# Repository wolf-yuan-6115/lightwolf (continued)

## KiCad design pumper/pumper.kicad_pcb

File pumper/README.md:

# Pumper

Pumper is an experimental RP2354-based USB Audio Class 2 DAC. The board uses a
PCM5102A DAC with OPA1652 and OPA1622 analog stages in a compact design intended
for learning about USB audio and DAC hardware.

The firmware provides a ten-band parametric EQ, headphone crossfeed, output
processing, USB host volume and mute, and persistent EQ profiles. Settings can
be controlled from either the React WebHID controller or the native Android
controller. Both controllers preview edits live and save persistent settings
only through explicit save actions.

## Supported audio formats

Pumper accepts stereo PCM over USB Audio Class 2 in the following formats:

| Sample rate | 16-bit stereo | Packed 24-bit stereo |
| ----------- | ------------- | -------------------- |
| 44.1 kHz    | Yes           | Yes                  |
| 48 kHz      | Yes           | Yes                  |
| 88.2 kHz    | Yes           | Yes                  |
| 96 kHz      | Yes           | Yes                  |
| 176.4 kHz   | Yes           | No                   |
| 192 kHz     | Yes           | No                   |

## Audio processing and hardware path

Audio packets cross from the USB-facing core into the real-time DSP core
through a fixed block pool. After processing, ping-pong DMA feeds the PIO I2S
transmitter; the analog stages then filter, buffer, attenuate, and drive the
headphone output.

```mermaid
flowchart TB
    HOST[USB host<br/>UAC2 stereo PCM]

    subgraph DIGITAL[Digital audio path]
        direction LR
        USB[TinyUSB on RP2354 core 0<br/>receive and decode USB packets]
        QUEUE[Fixed audio-block queue<br/>core 0 to core 1]
        EQ[Preamp and<br/>10-band parametric EQ]
        XF[Headphone crossfeed]
        HOSTCTL[USB host<br/>gain and mute]
        OUTPROC[Output processing<br/>balance, mono, and width]
        LIMIT[Always-on<br/>stereo limiter]
        PACK[Final PCM quantization<br/>and I2S packing]
        I2S[Ping-pong DMA and PIO<br/>I2S transmitter]
        DAC[PCM5102A<br/>I2S DAC]

        USB --> QUEUE --> EQ --> XF --> HOSTCTL --> OUTPROC --> LIMIT --> PACK --> I2S --> DAC
    end

    subgraph ANALOG[Analog audio path]
        direction LR
        FILTER[Passive output filters]
        BUFFER[OPA1652<br/>stereo buffer]
        VOLUME[Dual-gang analog<br/>volume control]
        DRIVER[OPA1622<br/>headphone driver]
        PROTECT[Output ESD protection]
        JACK[3.5 mm TRRS<br/>analog output]

        FILTER --> BUFFER --> VOLUME --> DRIVER --> PROTECT --> JACK
    end

    HOST --> USB
    DAC --> FILTER
```

## Repository layout

- [`firmware/`](firmware/) — RP2354 firmware and portable host tests.
- [`web/`](web/) — React/TypeScript WebHID controller.
- [`android/`](android/) — experimental Android USB-host controller.
- [`assets/`](assets/) — board and assembled-device images.
- KiCad source files in the repository root — schematic and PCB design.

## Build and run

### Firmware

The firmware requires the Pico SDK, CMake, Ninja, a native C compiler, and the
Arm GNU embedded toolchain. See [`firmware/README.md`](firmware/README.md) for
SDK setup, supported audio formats, flashing, and troubleshooting.

```sh
export PICO_SDK_PATH="${HOME}/Projects/pico-sdk"
cmake -S firmware -B firmware/build -G Ninja \
  -DCMAKE_BUILD_TYPE=Release \
  -DPICO_BOARD=pico2 \
  -DPICO_PLATFORM=rp2350-arm-s \
  -DPICO_FLASH_SIZE_BYTES=2097152
cmake --build firmware/build --target rp2350_usb_dac -j
```

Flash `firmware/build/rp2350_usb_dac.uf2` using the RP2354 BOOTSEL drive.

### Web controller

Use a Chromium-based browser. WebHID works on a secure origin and on
`http://localhost`.

```sh
cd web
pnpm install
pnpm dev
```

See [`web/README.md`](web/README.md) for Linux HID permissions, tests,
production builds, previewing, and deployment.

### Android controller

The Android controller requires JDK 17 and Android SDK API 37. Android Studio
can open [`android/`](android/) directly.

```sh
cd android
./gradlew testDebugUnitTest lintDebug assembleDebug
```

See [`android/README.md`](android/README.md) for the debug simulator and USB
device requirements.

### Firmware host tests

These tests do not require the Pico SDK:

```sh
cmake -S firmware/tests -B /tmp/pumper-firmware-tests
cmake --build /tmp/pumper-firmware-tests
ctest --test-dir /tmp/pumper-firmware-tests --output-on-failure
```

## Hardware

## Bill of materials

| Item         | Cost        |
| ------------ | ----------- |
| PCB shipping | $6.12       |
| PCB assembly | $86.18      |
| PCB          | $11.43      |
| **Total**    | **$103.73** |

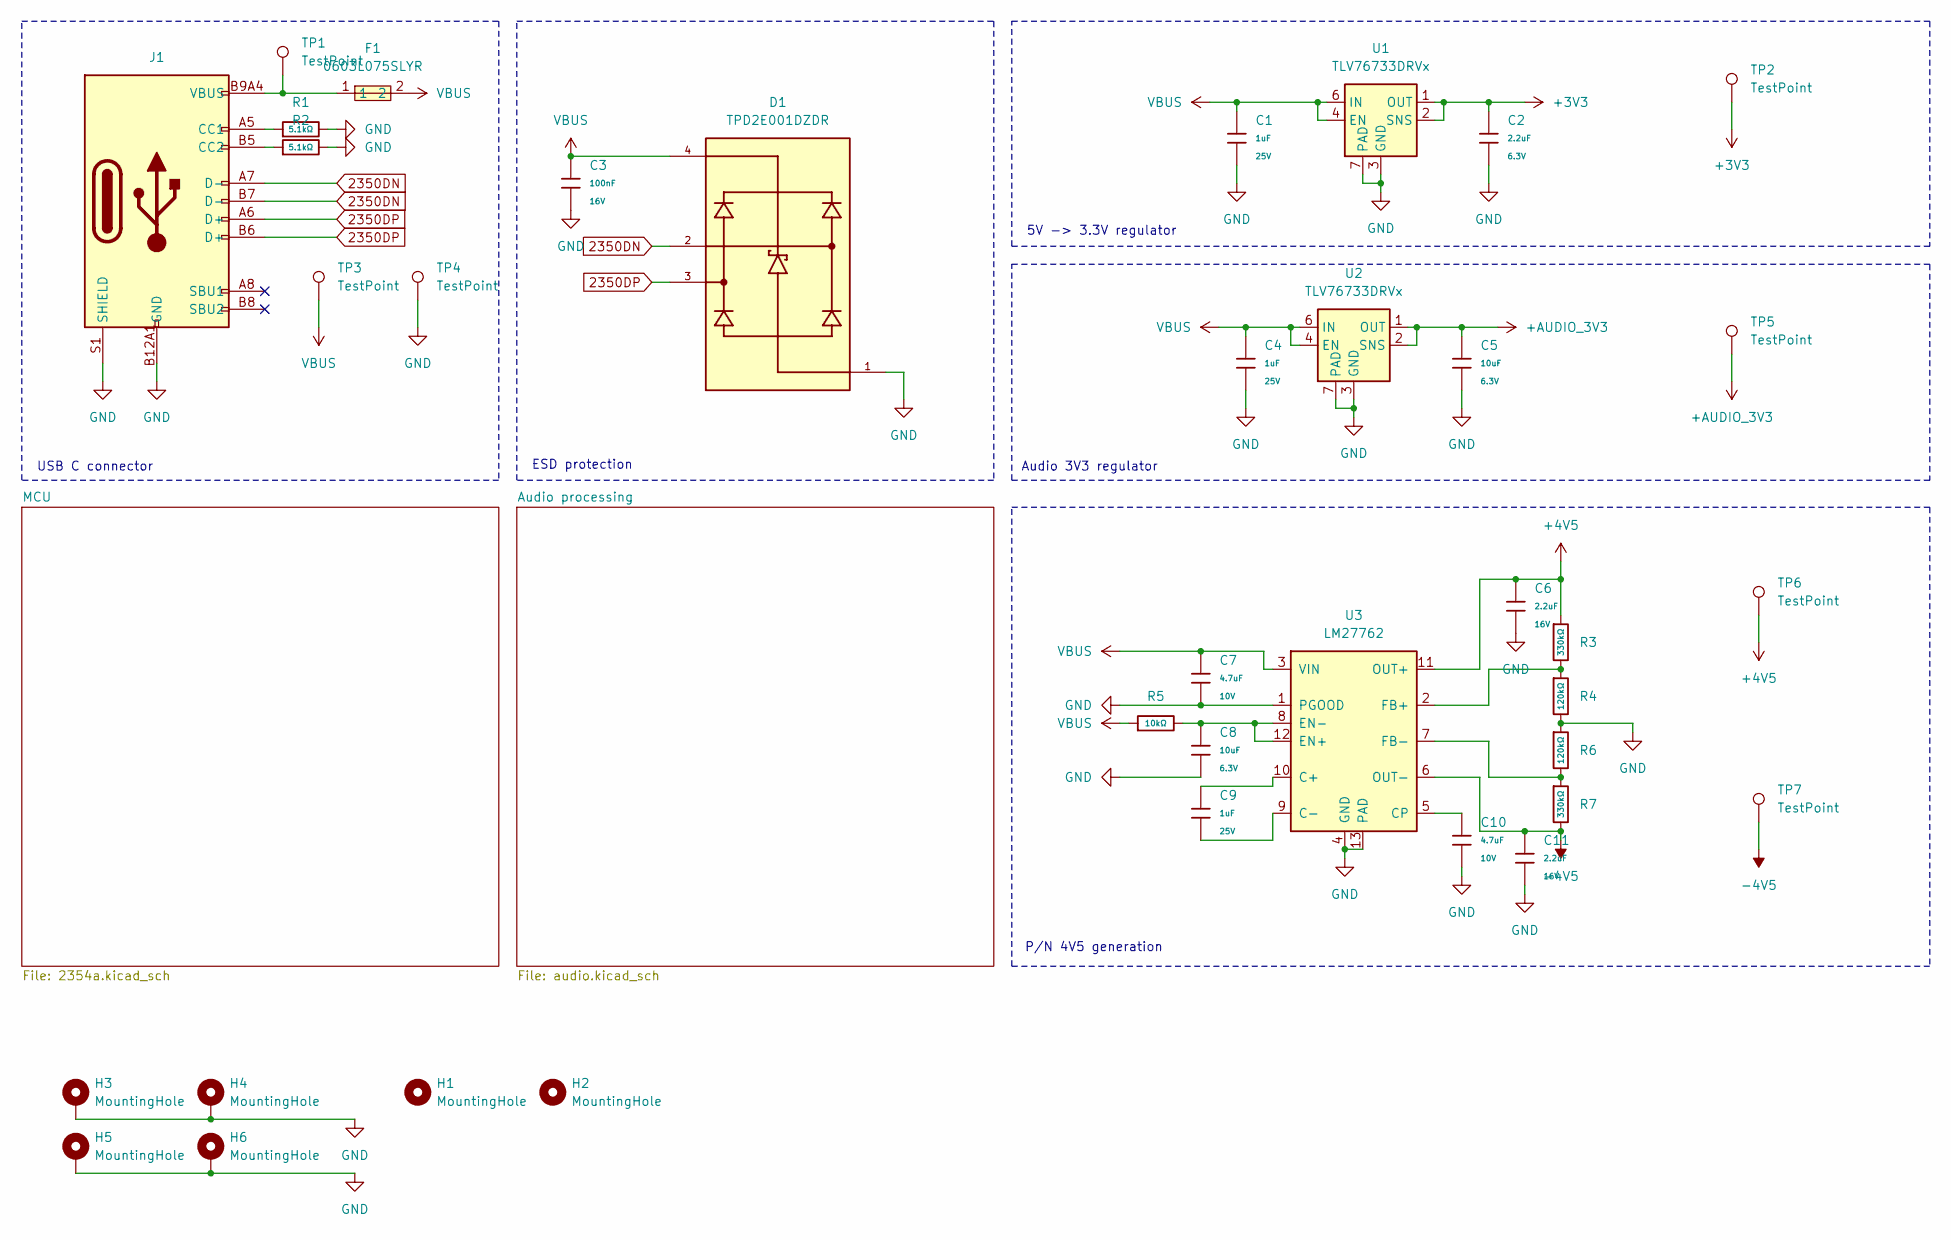
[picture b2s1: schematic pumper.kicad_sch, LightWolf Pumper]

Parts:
C1, C4, C9: 1uF; C_0402; Voltage Rated 25V; Tolerance ±10%; Part CL05A105KA5NQNC; LCSC C52923
C2: 2.2uF; C_0402; Voltage Rated 6.3V; Tolerance ±20%; Part CL05A225MQ5NSNC; LCSC C12530
C3: 100nF; C_0402; Voltage Rated 16V; Tolerance ±10%; Part CL05B104KO5NNNC; LCSC C1525
C5, C8: 10uF; C_0402; Voltage Rated 6.3V; Tolerance ±20%; Part CL05A106MQ5NUNC; LCSC C15525
C6, C11: 2.2uF; C_0603; Voltage Rated 16V; Tolerance ±10%; Part CL10A225KO8NNNC; LCSC C23630
C7, C10: 4.7uF; C_0402; Voltage Rated 10V; Tolerance ±20%; Part CL05A475MP5NRNC; LCSC C23733
D1: TPD2E001DZDR; SOT192P237X122-4N; PARTREV I
F1: 0603L075SLYR; F0603; LCSC Part C207016
H1, H2: MountingHole; ToolingHole_1.152mm
H3, H4, H5, H6: MountingHole; MountingHole_2.2mm_M2_Pad_Via
J1: Connector, USB-TYPE-C-16P; TYPE-C-SMD_HX-TYPE-C-16PIN; LCSC C2927039
R1, R2: 5.1kΩ; R_0402; Overload Voltage (Max) 50V; Tolerance ±1%; Part 0402WGF5101TCE; LCSC C25905
R3, R7: 330kΩ; R_0402; Overload Voltage (Max) 50V; Tolerance ±1%; Part 0402WGF3303TCE; LCSC C25778
R4, R6: 120kΩ; R_0402; Overload Voltage (Max) 50V; Tolerance ±1%; Part 0402WGF1203TCE; LCSC C25750
R5: 10kΩ; R_0402; Overload Voltage (Max) 50V; Tolerance ±1%; Part 0402WGF1002TCE; LCSC C25744
TP1, TP2, TP3, TP4, TP5, TP6, TP7: TestPoint; TestPoint_Pad_D1.0mm
U1, U2: TLV76733DRVx; WSON-6-1EP_2x2mm_P0.65mm_EP1x1.6mm_ThermalVias
U3: LM27762; WSON-12-1EP_3x2mm_P0.5mm_EP1x2.65_ThermalVias

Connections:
2350DN: D1.2, J1.A7 (D-), J1.B7 (D-); also elsewhere on the board
2350DP: D1.3, J1.A6 (D+), J1.B6 (D+); also elsewhere on the board
+3V3: C2.1, TP2.1, U1.1 (OUT), U1.2 (SNS); also elsewhere on the board
+4V5: C6.1, R3.1, TP6.1, U3.11 (OUT+); also elsewhere on the board
+AUDIO_3V3: C5.1, TP5.1, U2.1 (OUT), U2.2 (SNS); also elsewhere on the board
-4V5: C11.1, R7.2, TP7.1, U3.6 (OUT-); also elsewhere on the board
GND: C1.2, C2.2, C3.2, C4.2, C5.2, C6.2, C7.2, C8.2, C10.2, C11.2, D1.1, H3.1, H4.1, H5.1, H6.1, J1.A12B1 (GND), J1.B12A1 (GND), J1.S1 (SHIELD), R1.2, R2.2, R4.2, R6.1, TP4.1, U1.3 (GND), U1.5 (GND), U1.7 (PAD), U2.3 (GND), U2.5 (GND), U2.7 (PAD), U3.1 (PGOOD), U3.4 (GND), U3.13 (PAD); also elsewhere on the board
unnamed: F1.1, J1.A9B4 (VBUS), J1.B9A4 (VBUS), TP1.1
unnamed: J1.A5 (CC1), R1.1
unnamed: J1.B5 (CC2), R2.1
unnamed: C9.1, U3.10 (C+)
unnamed: C9.2, U3.9 (C-)
unnamed: C10.1, U3.5 (CP)
unnamed: C8.1, R5.2, U3.8 (EN-), U3.12 (EN+)
unnamed: R3.2, R4.1, U3.2 (FB+)
unnamed: R6.2, R7.1, U3.7 (FB-)
VBUS: C1.1, C3.1, C4.1, C7.1, D1.4, F1.2, R5.1, TP3.1, U1.4 (EN), U1.6 (IN), U2.4 (EN), U2.6 (IN), U3.3 (VIN)

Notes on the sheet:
ESD protection
Audio 3V3 regulator
P/N 4V5 generation
USB C connector
5V -> 3.3V regulator

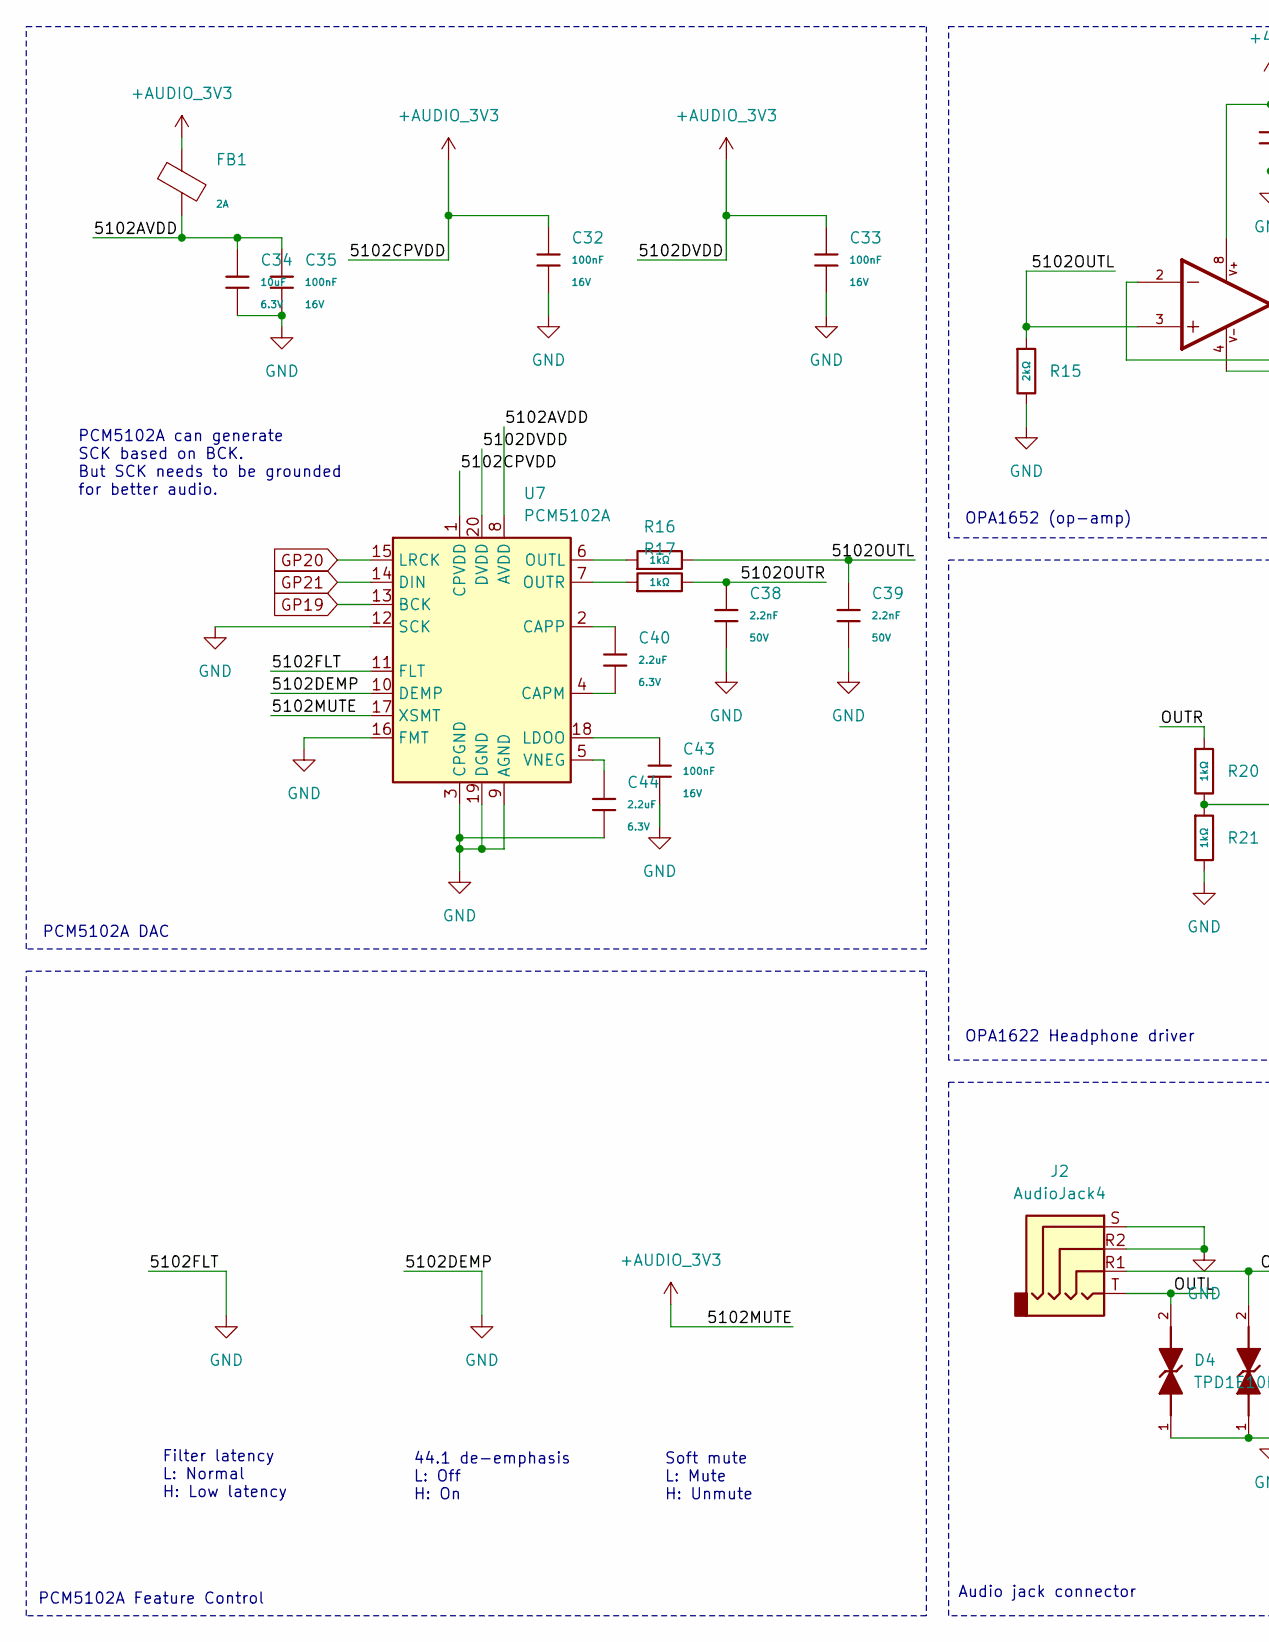
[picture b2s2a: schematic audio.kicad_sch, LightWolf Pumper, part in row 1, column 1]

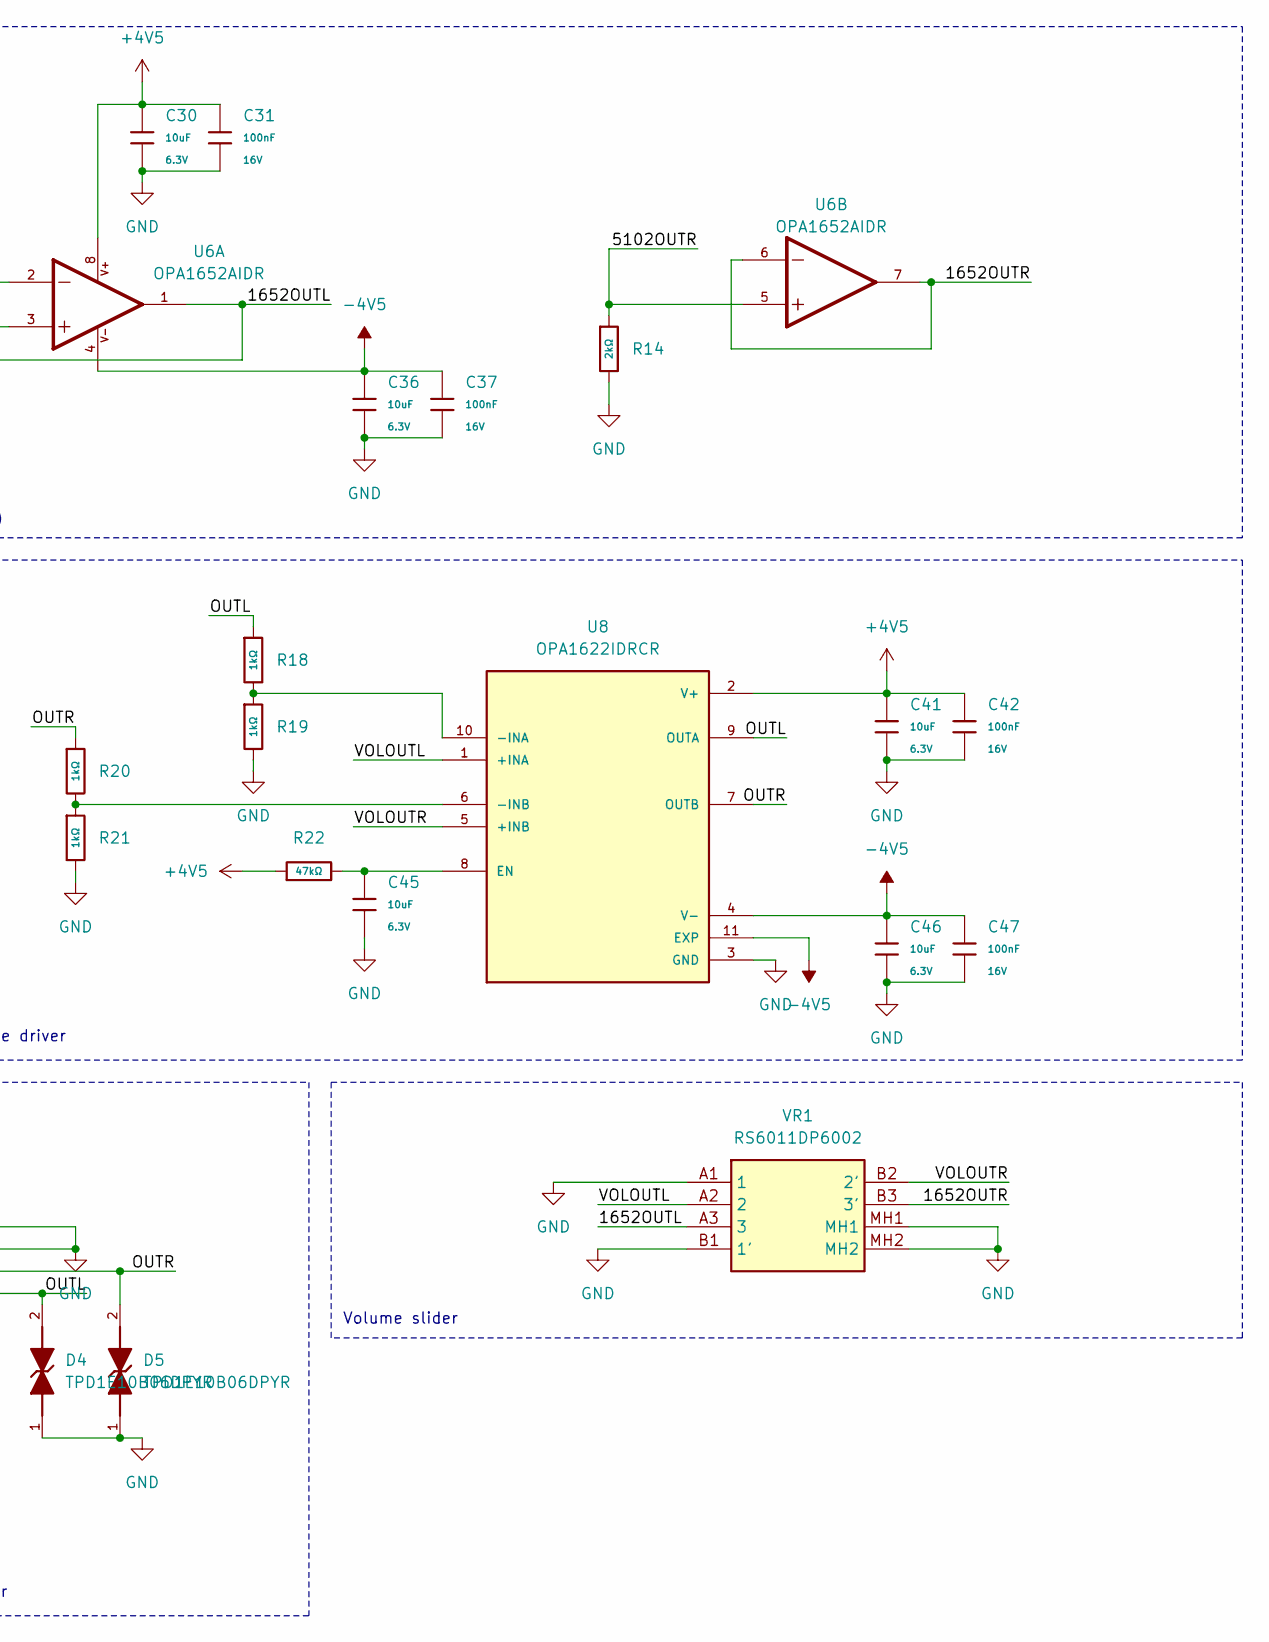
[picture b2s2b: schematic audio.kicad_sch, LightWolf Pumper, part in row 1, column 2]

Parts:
C30, C34, C36, C41, C45, C46: 10uF; C_0402; Voltage Rated 6.3V; Tolerance ±20%; Part CL05A106MQ5NUNC; LCSC C15525
C31, C32, C33, C35, C37, C42, C43, C47: 100nF; C_0402; Voltage Rated 16V; Tolerance ±10%; Part CL05B104KO5NNNC; LCSC C1525
C38, C39: 2.2nF; C_0402; Voltage Rated 50V; Tolerance ±10%; Part 0402B222K500NT; LCSC C1531
C40, C44: 2.2uF; C_0402; Voltage Rated 6.3V; Tolerance ±20%; Part CL05A225MQ5NSNC; LCSC C12530
D4, D5: TPD1E10B06DPYR; DIO_TPD1E10B06DPYR; PARTREV G
FB1: FB_0603; Current Rating 2A; Tolerance ±25%; Part BLM18PG121SN1D; LCSC C14709
J2: AudioJack4; Jack_3.5mm_KoreanHropartsElec_PJ-320D-4A_Horizontal
R14, R15: 2kΩ; R_0402; Overload Voltage (Max) 50V; Tolerance ±1%; Part 0402WGF2001TCE; LCSC C4109
R16, R17, R18, R19, R20, R21: 1kΩ; R_0402; Overload Voltage (Max) 50V; Tolerance ±1%; Part 0402WGF1001TCE; LCSC C11702
R22: 47kΩ; R_0402; Overload Voltage (Max) 50V; Tolerance ±1%; Part 0402WGF4702TCE; LCSC C25792
U6: OPA1652AIDR; SOIC127P599X175-8N; PARTREV B
U7: PCM5102A; TSSOP-20_4.4x6.5mm_P0.65mm
U8: OPA1622IDRCR; IC_OPA1622IDRCR; PARTREV B; DigiKey_Part_Number 296-45038-1-ND
VR1: RS6011DP6002; Mouser Part Number 688-RS6011DP6002

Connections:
+4V5: C30.1, C31.1, C41.1, C42.1, R22.1, U6.8, U8.2 (V+); also elsewhere on the board
+AUDIO_3V3: C32.1, C33.1, FB1.1, U7.1 (CPVDD), U7.17 (XSMT), U7.20 (DVDD); also elsewhere on the board
-4V5: C36.1, C37.1, C46.1, C47.1, U6.4, U8.4 (V-), U8.11 (EXP), U8.12 (EXP), U8.13 (EXP), U8.14 (EXP), U8.15 (EXP); also elsewhere on the board
/Audio processing/1652OUTL: U6.1, U6.2, VR1.A3 (3)
/Audio processing/1652OUTR: U6.6, U6.7, VR1.B3 (3')
/Audio processing/5102AVDD: C34.1, C35.1, FB1.2, U7.8 (AVDD)
/Audio processing/5102OUTL: C39.1, R15.1, R16.2, U6.3
/Audio processing/5102OUTR: C38.1, R14.1, R17.2, U6.5
/Audio processing/OUTL: D4.2, J2.T, R18.1, U8.9 (OUTA)
/Audio processing/OUTR: D5.2, J2.R1, R20.1, U8.7 (OUTB)
/Audio processing/VOLOUTL: U8.1 (+INA), VR1.A2 (2)
/Audio processing/VOLOUTR: U8.5 (+INB), VR1.B2 (2')
GND: C30.2, C31.2, C32.2, C33.2, C34.2, C35.2, C36.2, C37.2, C38.2, C39.2, C41.2, C42.2, C43.2, C44.2, C45.2, C46.2, C47.2, D4.1, D5.1, J2.R2, J2.S, R14.2, R15.2, R19.2, R21.2, U7.3 (CPGND), U7.9 (AGND), U7.10 (DEMP), U7.11 (FLT), U7.12 (SCK), U7.16 (FMT), U7.19 (DGND), U8.3 (GND), VR1.A1 (1), VR1.B1 (1'), VR1.MH1, VR1.MH2; also elsewhere on the board
GP19: U7.13 (BCK); also elsewhere on the board
GP20: U7.15 (LRCK); also elsewhere on the board
GP21: U7.14 (DIN); also elsewhere on the board
unnamed: C40.2, U7.4 (CAPM)
unnamed: C40.1, U7.2 (CAPP)
unnamed: C43.1, U7.18 (LDOO)
unnamed: R16.1, U7.6 (OUTL)
unnamed: R17.1, U7.7 (OUTR)
unnamed: C44.1, U7.5 (VNEG)
unnamed: R18.2, R19.1, U8.10 (-INA)
unnamed: R20.2, R21.1, U8.6 (-INB)
unnamed: C45.1, R22.2, U8.8 (EN)

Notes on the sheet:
Audio jack connector
OPA1622 Headphone driver
PCM5102A DAC
Soft mute L: Mute H: Unmute
Filter latency L: Normal H: Low latency
44.1 de-emphasis L: Off H: On
OPA1652 (op-amp)
PCM5102A Feature Control
Volume slider
PCM5102A can generate SCK based on BCK. But SCK needs to be grounded for better audio.

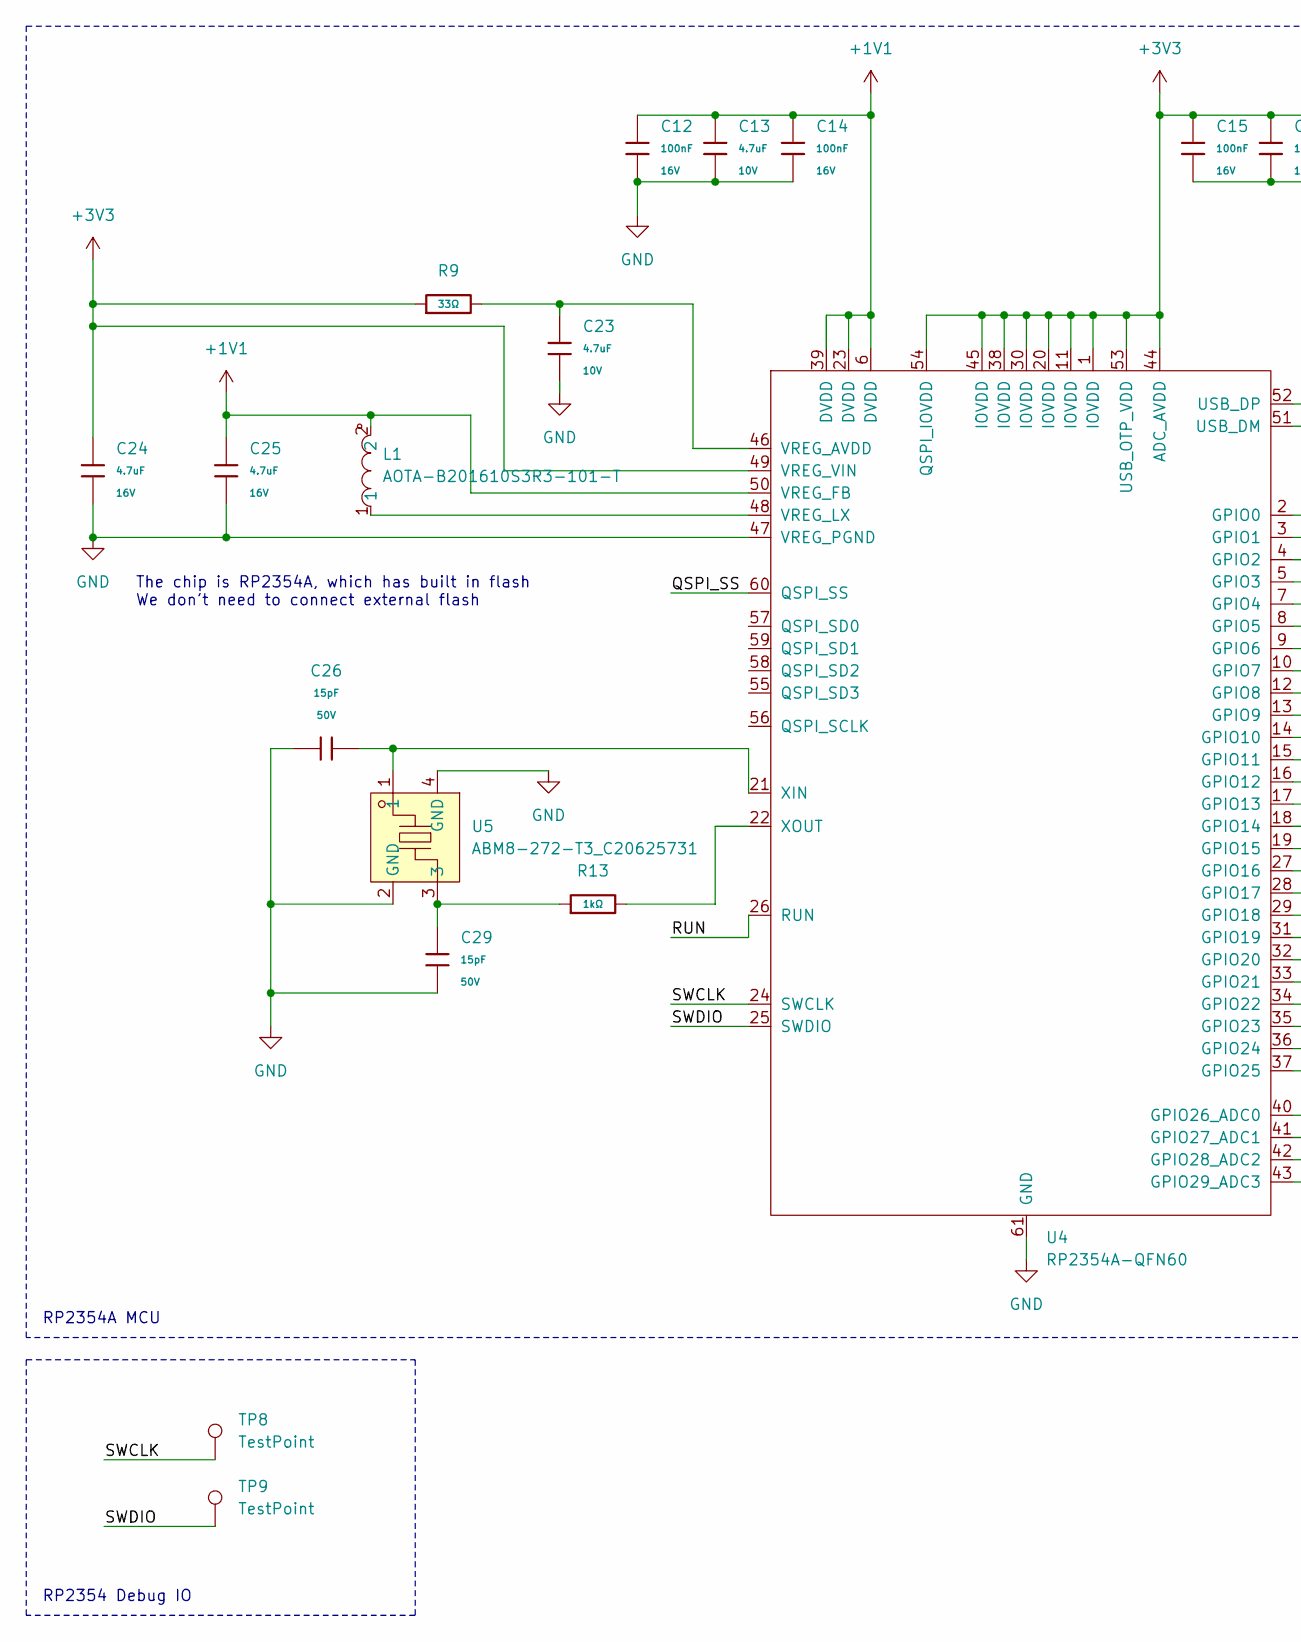
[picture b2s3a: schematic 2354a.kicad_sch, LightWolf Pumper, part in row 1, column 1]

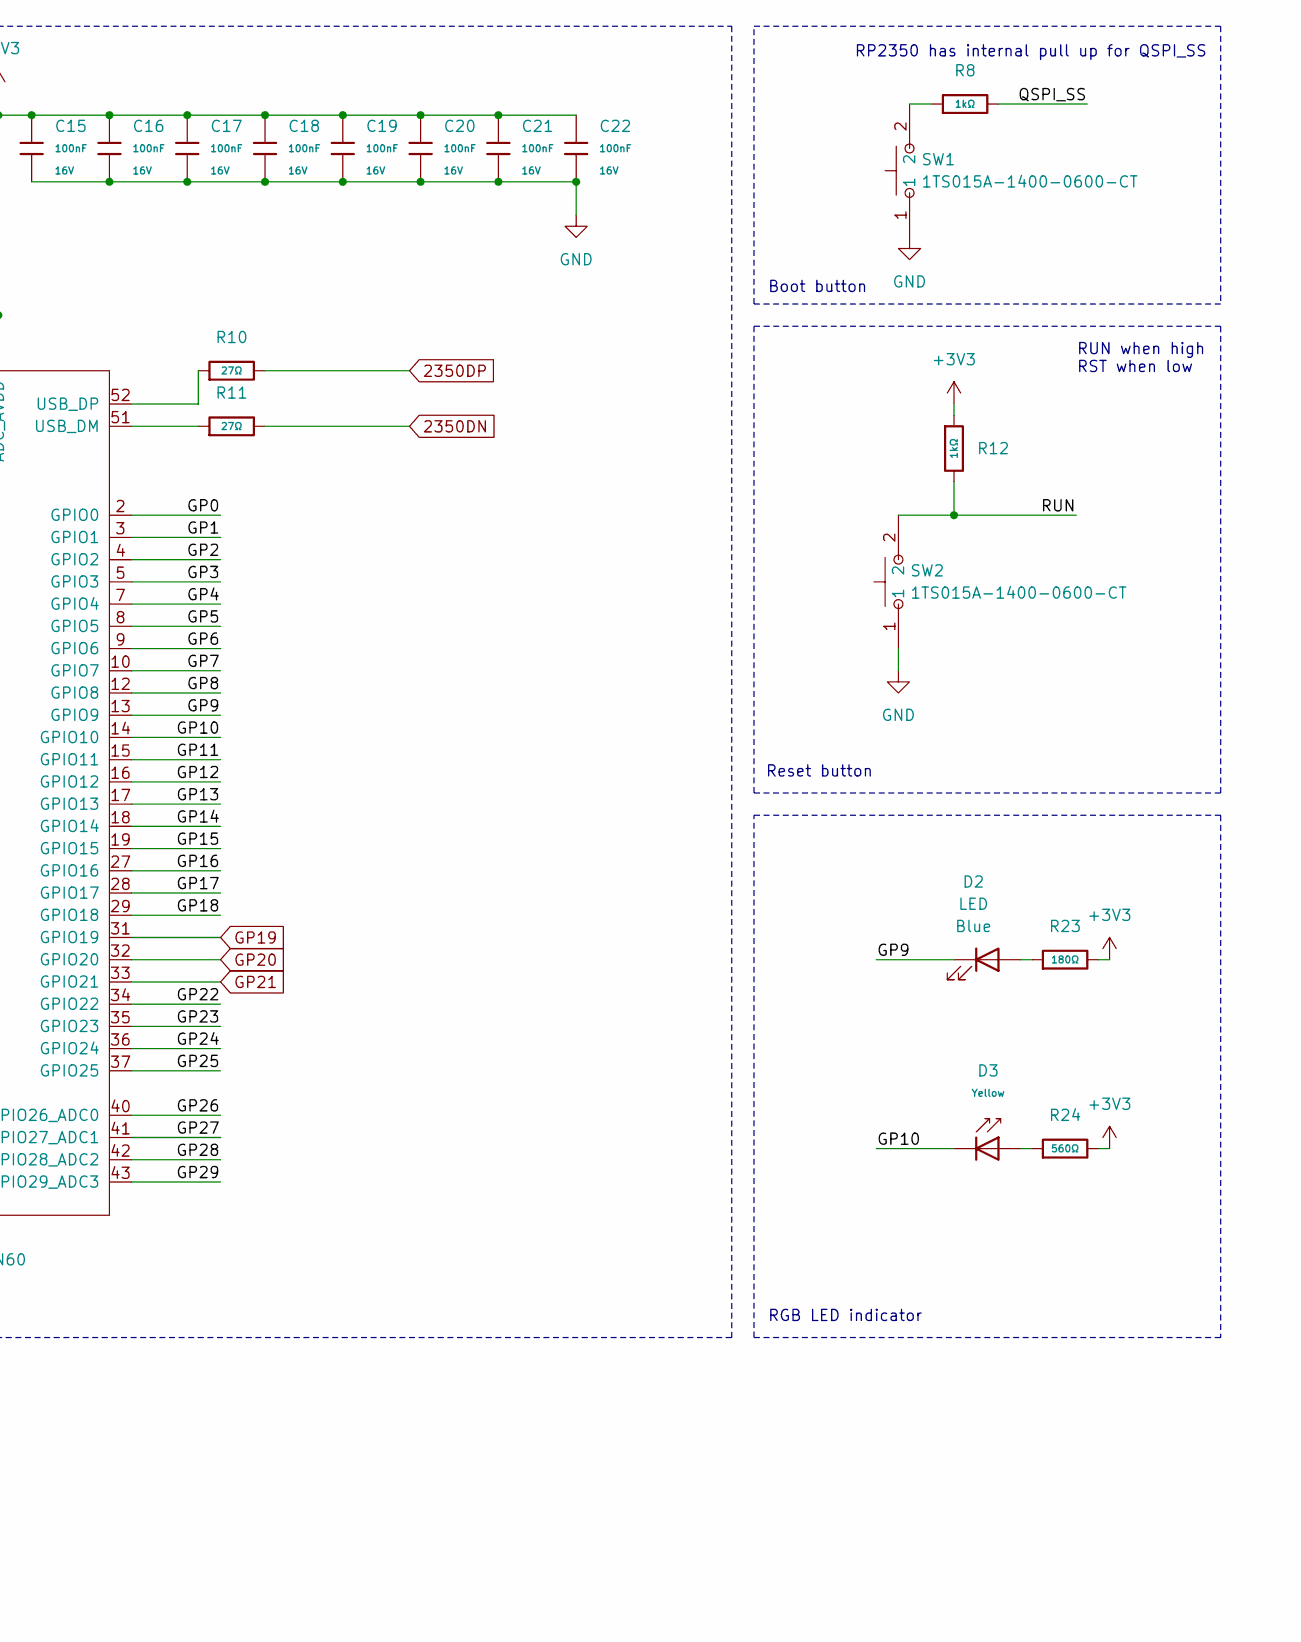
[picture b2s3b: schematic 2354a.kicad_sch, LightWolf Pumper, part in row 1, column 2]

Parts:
C12, C14, C15, C16, C17, C18, C19, C20, C21, C22: 100nF; C_0402; Voltage Rated 16V; Tolerance ±10%; Part CL05B104KO5NNNC; LCSC C1525
C13, C23: 4.7uF; C_0402; Voltage Rated 10V; Tolerance ±20%; Part CL05A475MP5NRNC; LCSC C23733
C24, C25: 4.7uF; C_0603; Voltage Rated 16V; Tolerance ±10%; Part CL10A475KO8NNNC; LCSC C19666
C26, C29: 15pF; C_0402; Voltage Rated 50V; Tolerance ±5%; Part 0402CG150J500NT; LCSC C1548
D2: LED; D_0603; LCSC C2288
D3: Yellow; D_0603; Forward Voltage (VF) 1.6V~2.6V; Part NCD0603Y2; LCSC C89811
L1: AOTA-B201610S3R3-101-T; IND-SMD_L2.0-W1.6_AOTA-B201610S3R3-101-T; LCSC Part C42411119
R8, R12, R13: 1kΩ; R_0402; Overload Voltage (Max) 50V; Tolerance ±1%; Part 0402WGF1001TCE; LCSC C11702
R9: 33Ω; R_0402; Overload Voltage (Max) 50V; Tolerance ±1%; Part 0402WGF330JTCE; LCSC C25105
R10, R11: 27Ω; R_0603; Overload Voltage (Max) 75V; Tolerance ±1%; Part 0603WAF270JT5E; LCSC C25190
R23: 180Ω; R_0603; Overload Voltage (Max) 75V; Tolerance ±1%; Part 0603WAF1800T5E; LCSC C22828
R24: 560Ω; R_0603; Overload Voltage (Max) 75V; Tolerance ±1%; Part 0603WAF5600T5E; LCSC C23204
SW1, SW2: 1TS015A-1400-0600-CT; SW-SMD_L3.0-W2.0-LS3.5; LCSC Part C319433
TP8, TP9: TestPoint; TestPoint_Pad_D1.0mm
U4: RP2354A-QFN60; QFN-60-1EP_7x7mm_P0.4mm_EP3.4x3.4mm_ThermalVias
U5: ABM8-272-T3_C20625731; CRYSTAL-SMD_4P-L3.2-W2.5-BL; LCSC Part C20625731

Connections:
2350DN: R11.2; also elsewhere on the board
2350DP: R10.2; also elsewhere on the board
+1V1: C12.1, C13.1, C14.1, C25.1, L1.2, U4.6 (DVDD), U4.23 (DVDD), U4.39 (DVDD), U4.50 (VREG_FB)
+3V3: C15.1, C16.1, C17.1, C18.1, C19.1, C20.1, C21.1, C22.1, C24.1, R9.1, R12.1, R23.2, R24.2, U4.1 (IOVDD), U4.11 (IOVDD), U4.20 (IOVDD), U4.30 (IOVDD), U4.38 (IOVDD), U4.44 (ADC_AVDD), U4.45 (IOVDD), U4.49 (VREG_VIN), U4.53 (USB_OTP_VDD), U4.54 (QSPI_IOVDD); also elsewhere on the board
/MCU/GP0: U4.2 (GPIO0)
/MCU/GP1: U4.3 (GPIO1)
/MCU/GP2: U4.4 (GPIO2)
/MCU/GP3: U4.5 (GPIO3)
/MCU/GP4: U4.7 (GPIO4)
/MCU/GP5: U4.8 (GPIO5)
/MCU/GP6: U4.9 (GPIO6)
/MCU/GP7: U4.10 (GPIO7)
/MCU/GP8: U4.12 (GPIO8)
/MCU/GP9: D2.1 (K), U4.13 (GPIO9)
/MCU/GP10: D3.1, U4.14 (GPIO10)
/MCU/GP11: U4.15 (GPIO11)
/MCU/GP12: U4.16 (GPIO12)
/MCU/GP13: U4.17 (GPIO13)
/MCU/GP14: U4.18 (GPIO14)
/MCU/GP15: U4.19 (GPIO15)
/MCU/GP16: U4.27 (GPIO16)
/MCU/GP17: U4.28 (GPIO17)
/MCU/GP18: U4.29 (GPIO18)
/MCU/GP22: U4.34 (GPIO22)
/MCU/GP23: U4.35 (GPIO23)
/MCU/GP24: U4.36 (GPIO24)
/MCU/GP25: U4.37 (GPIO25)
/MCU/GP26: U4.40 (GPIO26_ADC0)
/MCU/GP27: U4.41 (GPIO27_ADC1)
/MCU/GP28: U4.42 (GPIO28_ADC2)
/MCU/GP29: U4.43 (GPIO29_ADC3)
/MCU/QSPI_SS: R8.2, U4.60 (QSPI_SS)
/MCU/RUN: R12.2, SW2.2, U4.26 (RUN)
/MCU/SWCLK: TP8.1, U4.24 (SWCLK)
/MCU/SWDIO: TP9.1, U4.25 (SWDIO)
GND: C12.2, C13.2, C14.2, C15.2, C16.2, C17.2, C18.2, C19.2, C20.2, C21.2, C22.2, C23.2, C24.2, C25.2, C26.1, C29.2, SW1.1, SW2.1, U4.47 (VREG_PGND), U4.61 (GND), U5.2 (GND), U5.4 (GND); also elsewhere on the board
GP19: U4.31 (GPIO19); also elsewhere on the board
GP20: U4.32 (GPIO20); also elsewhere on the board
GP21: U4.33 (GPIO21); also elsewhere on the board
unnamed: C29.1, R13.1, U5.3
unnamed: D2.2 (A), R23.1
unnamed: D3.2, R24.1
unnamed: R8.1, SW1.2
unnamed: R11.1, U4.51 (USB_DM)
unnamed: R10.1, U4.52 (USB_DP)
unnamed: C23.1, R9.2, U4.46 (VREG_AVDD)
unnamed: L1.1, U4.48 (VREG_LX)
unnamed: C26.2, U4.21 (XIN), U5.1
unnamed: R13.2, U4.22 (XOUT)

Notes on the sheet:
The chip is RP2354A, which has built in flash We don't need to connect external flash
Reset button
RP2354A MCU
RP2354 Debug IO
RUN when high RST when low
Boot button
RP2350 has internal pull up for QSPI_SS
RGB LED indicator

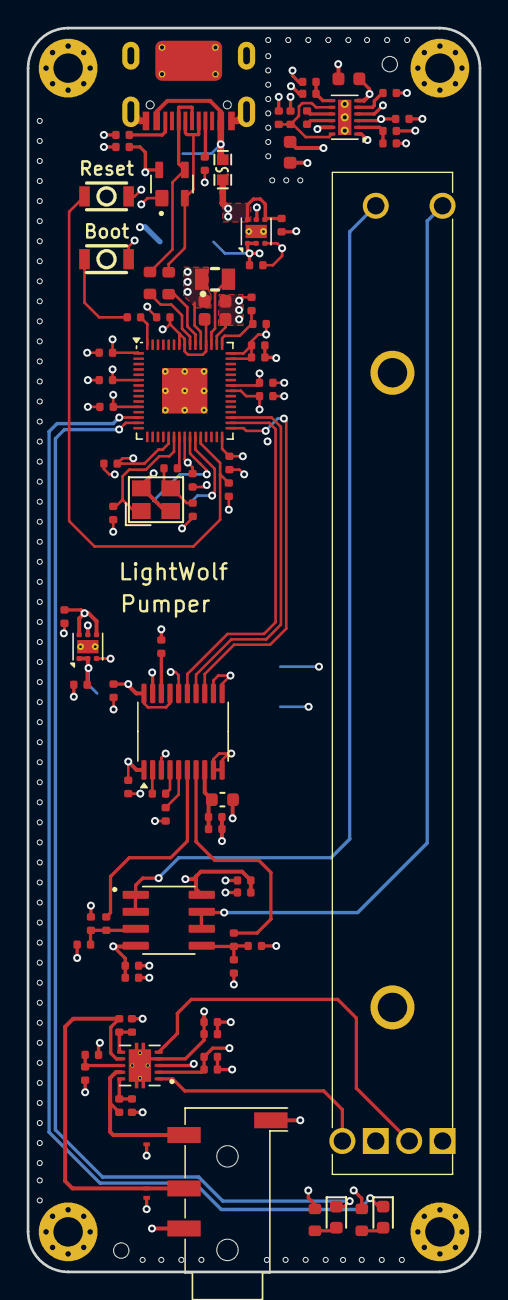
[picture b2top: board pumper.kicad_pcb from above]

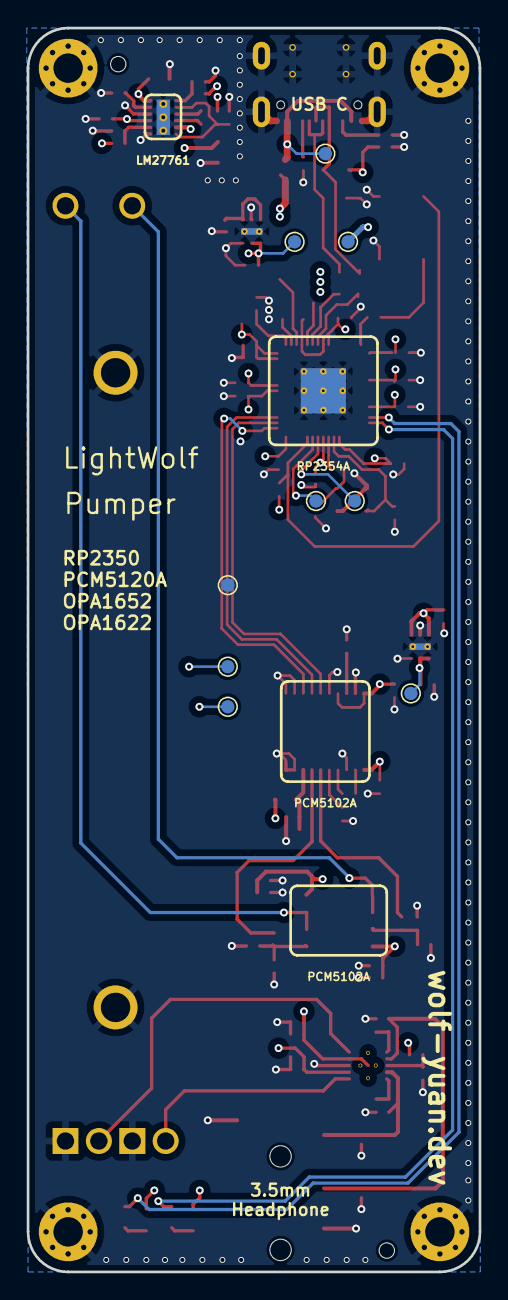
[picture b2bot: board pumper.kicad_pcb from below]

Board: 4 copper layers, 33.8 x 93.1 mm, 105 parts (9 on the bottom side), 55 nets.

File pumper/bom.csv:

Comment,Designator,Footprint,LCSC,Quantity
0603L075SLYR,F1,F0603,C207016,1
100nF,"C12,C14,C15,C16,C17,C18,C19,C20,C21,C22,C27,C28,C3,C31,C32,C33,C35,C37,C42,C43,C47",C_0402,C1525,21
10kΩ,R5,R_0402,C25744,1
10uF,"C30,C34,C36,C41,C45,C46,C5,C8",C_0402,C15525,8
120kΩ,"R4,R6",R_0402,C25750,2
15pF,"C26,C29",C_0402,C1548,2
1TS015A-1400-0600-CT,"SW1,SW2",SW-SMD_L3.0-W2.0-LS3.5,C319433,2
1kΩ,"R12,R13,R16,R17,R18,R19,R20,R21,R8",R_0402,C11702,9
1uF,"C1,C4,C9",C_0402,C52923,3
2.2nF,"C38,C39",C_0402,C1531,2
2.2uF,"C2,C40,C44",C_0402,C12530,3
2.2uF,"C11,C6",C_0603,C23630,2
27Ω,"R10,R11",R_0603,C25190,2
2kΩ,"R14,R15",R_0402,C4109,2
330kΩ,"R3,R7",R_0402,C25778,2
33Ω,R9,R_0402,C25105,1
4.7uF,"C24,C25",C_0603,C19666,2
4.7uF,"C10,C13,C23,C7",C_0402,C23733,4
47kΩ,R22,R_0402,C25792,1
5.1kΩ,"R1,R2",R_0402,C25905,2
ABM8-272-T3_C20625731,U5,CRYSTAL-SMD_4P-L3.2-W2.5-BL,C20625731,1
AOTA-B201610S3R3-101-T,L1,IND-SMD_L2.0-W1.6_AOTA-B201610S3R3-101-T,C42411119,1
AudioJack4,J2,Jack_3.5mm_KoreanHropartsElec_PJ-320D-4A_Horizontal,C95562,1
"Connector, USB-TYPE-C-16P",J1,TYPE-C-SMD_HX-TYPE-C-16PIN,C5178539,1
LM27762,U3,WSON-12-1EP_3x2mm_P0.5mm_EP1x2.65_ThermalVias,C473398,1
OPA1622IDRCR,U8,IC_OPA1622IDRCR,C2876559,1
OPA1652AIDR,U6,SOIC127P599X175-8N,C30025,1
PCM5102A,U7,TSSOP-20_4.4x6.5mm_P0.65mm,C107671,1
RP2354A-QFN60,U4,QFN-60-1EP_7x7mm_P0.4mm_EP3.4x3.4mm_ThermalVias,C41378174,1
RS6011DP6002,VR1,RS6011DP6002,C470553,1
TLV76733DRVx,"U1,U2",WSON-6-1EP_2x2mm_P0.65mm_EP1x1.6mm_ThermalVias,C2848334,2
TPD1E10B06DPYR,"D4,D5",DIO_TPD1E10B06DPYR,C48260,2
TPD2E001DZDR,D1,SOT192P237X122-4N,C89411,1
WS2812B,"D2,D3",LED-SMD_4P-L1.6-W1.5_XL-1615RGBC-WS2812B,C5349954,2
~,FB1,FB_0603,C1002,1
